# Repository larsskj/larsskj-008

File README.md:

An effects board for light, motion, and sound
=============================================

### larsskj-008

This board is basically a wrapper to provide an easy interface to an Arduino Nano, a DFPlayer Mini, and some support circuitry. It provides two inputs for the Arduino, outputs for a speaker, and two FET controlled outputs for LEDs and/or motors.

If you just need input and sound, the setup can run directly from USB power supplied to the Arduino. Otherwise there's a terminal block that allows supply of 5V DC for the Arduino and the DFPlayer. It also allows for a 12V DC supply that will drive the FET outputs - it can actually be just about any reasonable voltage and isn't restricted to 12V. 

I use the board to emit sounds and control moving chickens for a henhouse, and for controlling light, sound, and servos for a railway crossing. 

For more information, visit the [project homepage](https://larsskj.org/projects/larsskj-008).

The files provided are project files for [KiCad 5](http://kicad-pcb.org/).

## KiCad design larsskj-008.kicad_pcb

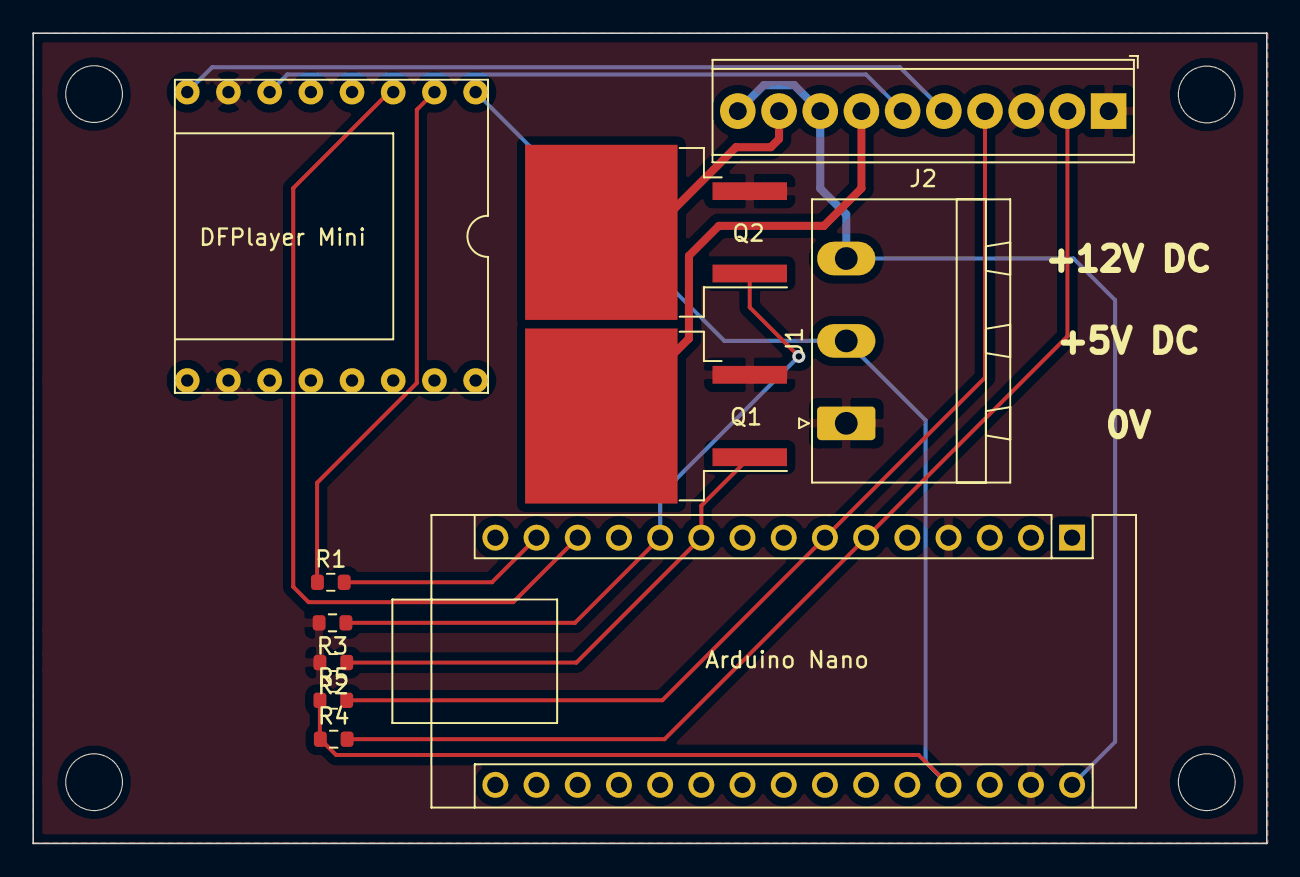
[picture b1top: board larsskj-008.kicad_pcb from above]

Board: 2 copper layers, 76.0 x 49.9 mm, 11 parts (0 on the bottom side), 14 nets.

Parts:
A1: Arduino Nano; Arduino_Nano
J1: Conn_01x03_Male; PhoenixContact_MSTBA_2,5_3-G-5,08_1x03_P5.08mm_Horizontal
J2: Conn_01x10; TerminalBlock_Phoenix_MPT-0,5-10-2.54_1x10_P2.54mm_Horizont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
Q1, Q2: IRF520; TO-263-2
R1, R2, R3: 1K0; R_0603_1608Metric
R4, R5: 10K; R_0603_1608Metric
U1: DFPlayer Mini; DFPlayer_V2

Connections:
GND: A1.4, A1.29, J1.1, J2.1, J2.3, Q1.3, Q2.3, R2.2, R3.2, U1.7, U1.10
unnamed: A1.6, J2.2, R4.2
unnamed: A1.7, J2.4, R5.2
unnamed: A1.10, Q1.1, R2.1
unnamed: A1.11, Q2.1, R3.1
unnamed: A1.13, U1.3
unnamed: A1.14, R1.2
unnamed: J2.5, U1.8
unnamed: J2.6, U1.6
unnamed: J2.7, Q1.2
unnamed: J2.9, Q2.2
unnamed: R1.1, U1.2
VCC: A1.30, J1.3, J2.8, J2.10
VDC: A1.27, J1.2, R4.1, R5.1, U1.1

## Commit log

2021-08-26 Code added.
